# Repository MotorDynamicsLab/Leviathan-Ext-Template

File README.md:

# Leviathan Extension Template

This project contains files that can be used to create your own custom Extension PCB for the Leviathan mainboard. 

## KiCad/ 
This directory contains a kicad project template that will get you started on creating a custom extension PCB

## CAD/
This directory contains 2D drawings and 3D models of the template PCB

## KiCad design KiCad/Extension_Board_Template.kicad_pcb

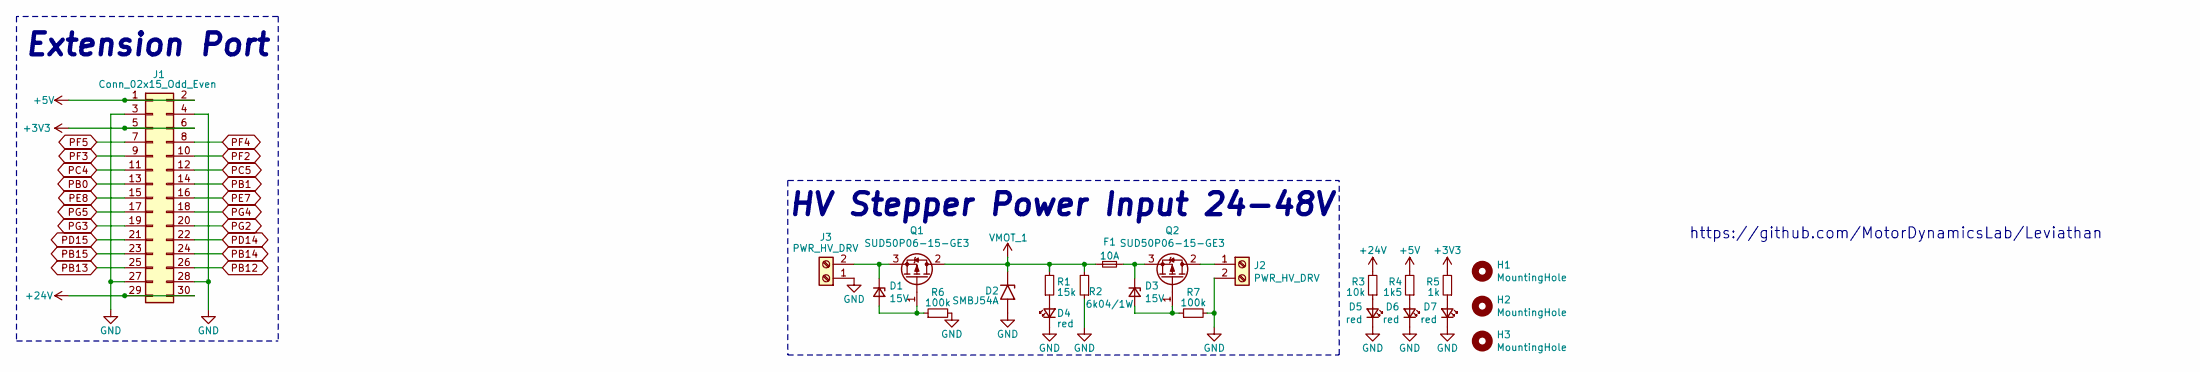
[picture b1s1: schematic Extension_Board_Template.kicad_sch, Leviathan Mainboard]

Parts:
D1, D3: 15V; D_SOD-123; LCSC C177014
D2: SMBJ54A; D_SMB; LCSC C353352
D4, D5, D6, D7: red; LED_0603_1608Metric; LCSC C434419
F1: 10A; Fuseholder_Littelfuse_Nano2_154x; LCSC C206921
H1, H2, H3: MountingHole; MountingHole_3.2mm_M3_Pad_TopBottom
J1: Conn_02x15_Odd_Even; PinHeader_2x15_P2.54mm_Horizontal
J2, J3: PWR_HV_DRV; TerminalBlock_Phoenix_MKDS-1,5-2_1x02_P5.00mm_Horizontal
Q1, Q2: SUD50P06-15-GE3; TO-252-2; LCSC C141584
R1: 15k; R_0603_1608Metric; LCSC C73802
R2: 6k04/1W; R_2512_6332Metric; LCSC C421527
R3: 10k; R_0603_1608Metric; LCSC# C384294
R4: 1k5; R_0603_1608Metric; LCSC C22843
R5: 1k; R_0603_1608Metric; LCSC C14676
R6, R7: 100k; R_0603_1608Metric; LCSC C14675

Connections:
+3V3: J1.5, J1.6, R5.2
+5V: J1.1, J1.2, R4.2
+24V: J1.29, J1.30, R3.2
GND: D2.2 (A2), D4.1 (K), D5.1 (K), D6.1 (K), D7.1 (K), J1.3, J1.4, J1.27, J1.28, J2.2, J3.1, R2.1, R6.2, R7.2
unnamed: D1.2 (A), Q1.1 (G), R6.1
unnamed: D1.1 (K), J3.2, Q1.3 (S)
unnamed: D3.2 (A), Q2.1 (G), R7.1
unnamed: D3.1 (K), F1.2, Q2.3 (S)
unnamed: D4.2 (A), R1.1
unnamed: D5.2 (A), R3.1
unnamed: D6.2 (A), R4.1
unnamed: D7.2 (A), R5.1
unnamed: J2.1, Q2.2 (D)
PB0: J1.13
PB1: J1.14
PB12: J1.26
PB13: J1.25
PB14: J1.24
PB15: J1.23
PC4: J1.11
PC5: J1.12
PD14: J1.22
PD15: J1.21
PE7: J1.16
PE8: J1.15
PF2: J1.10
PF3: J1.9
PF4: J1.8
PF5: J1.7
PG2: J1.20
PG3: J1.19
PG4: J1.18
PG5: J1.17
VMOT_1: D2.1 (A1), F1.1, Q1.2 (D), R1.2, R2.2

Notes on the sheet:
Extension Port
HV Stepper Power Input 24-48V
https://github.com/MotorDynamicsLab/Leviathan

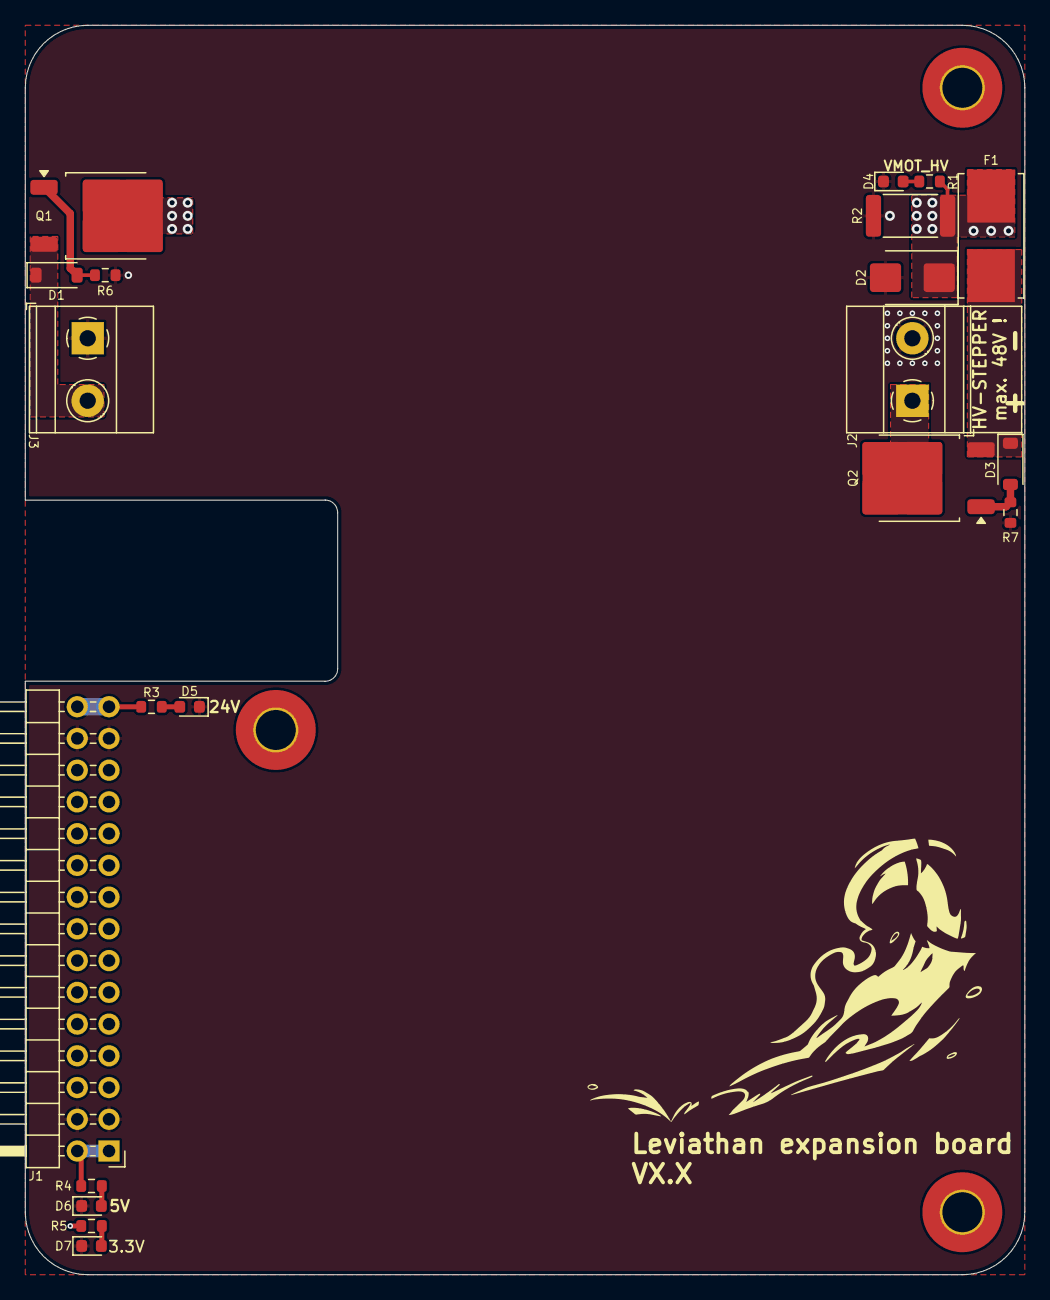
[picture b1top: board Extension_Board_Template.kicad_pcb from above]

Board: 4 copper layers, 80.0 x 100.0 mm, 23 parts (0 on the bottom side), 14 nets.

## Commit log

2025-01-24 initial commit of template project
2025-01-24 update fill zone in layout
2025-01-24 add CAD directory and README.md
2025-02-19 add 3D rendering image
2025-02-19 add image to README.md
2025-05-12 rename project_source/ to KiCad/
2025-05-12 update to KiCAD 9 format
2026-01-21 Create LICENSE
